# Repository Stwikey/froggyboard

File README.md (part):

# Keroppi

A cozy keyboard with every add-on you can think of! Keroppi is a wired keyboard, powered by a Raspberry Pi Pico through a modern USB-C port. It resembles a 75% keyboard layout style with 79 keys and also features a rotary encoder that can be used to toggle many short cuts such as turning the volume up or down. It also acts as another switch! There is also a TFT LCD screen that can display all sorts of images as you type! Finally, Keroppi has per key RGB lighting, and plays cool lighting animations on the keyboard!

# What does Keroppi do?

Keroppi is a wired keyboard that can be connected to your computer so you can start typing comfortably! it comes with cool components such as per-key RGB backlighting that plays animations as you type, a rotary encoder, and a TFT LCD screen that can display cool images or animations! Keroppi was designed to be an "all in one" keyboard, at least it's everything that I would want in a keyboard :D

# Why does Keroppi exist?

I've never owned a keyboard before despite being on my computer all day so I thought this was the perfect time to make one from scratch! Plus I'd be able to add as many features as I want and completely personalize it :D

# How do you use Keroppi?

## Assembly Instructions

#### 1. Handsoldering the PCB

Start by assembling the PCB! Handsolder all of the components onto the the PCB board according to the silkscreen diagram, that includes any LEDs, capacitors, resistors, pin headers, Raspberry Pi Pico, USB-C, TFT LCD, rotary encoder, and hotswap sockets.

The bottom should look something like this

The top should look something like this 

#### 1.5. Soldering the Data Lines

Twist two jumper wires together, trying to keep them the same length. Solder one of the jumper wires from TP2 on the Raspberry Pi Pico to D- and a jumper wire from TP3 on the Raspberry Pi Pico to D+ to connect the data lines.

Please note that although this method can work, it is still risky as data may not be able to establish a reliable connection. If this happens and you see data is not being transferred well, you can simply just use the usb port instead of the usb-c port.

#### 2. Assembling the Switch Plate

Assemble the switch plate by sliding in the stabilizers to their respective mounts

#### 3. Attach the Base

Install M2 female–male hex spacers in the base mounting holes and space out the switch plate from the PCB using 4mm spacers, next screw the layers in using a M2 screws inserted from the switch plate

#### 4. Attach the top plate

Slide in the top plate and it should hold screwless using friction! 

#### 5. Insert the switches

You can now insert the switches through the hotswap sockets

#### 6. Attach the keycaps

Attach the keycaps onto the switches

#### 7. Flashing Firmware

Simply start by putting the Raspberry Pi Pico into bootloader mode by plugging it into a USB port and pressing down the BOOTSEL button, once you see RPI-RPI2 open on your computer, drag the frogboard_default.uf2 file onto it (found in the firmware folder of this github repository) and you are ready to start typing!

# Schematic

## Switch Matrix

## RGB Daisy Chain

## Other Components

# PCB

## 3D Viewer Front

## 3D Viewer Back

# 3D Model

# BOM

|Item                                    |Qty Required|Qty*|Unit Price(CAD)|Total Price(CAD)**|URL                                                                                                                                                                                                                                                                                                                                                                                                                                                                                                                                                                                                                                                                                                                                                                                                                                                                                                                                                                              |
|----------------------------------------|------------|----|---------------|------------------|---------------------------------------------------------------------------------------------------------------------------------------------------------------------------------------------------------------------------------------------------------------------------------------------------------------------------------------------------------------------------------------------------------------------------------------------------------------------------------------------------------------------------------------------------------------------------------------------------------------------------------------------------------------------------------------------------------------------------------------------------------------------------------------------------------------------------------------------------------------------------------------------------------------------------------------------------------------------------------|
|Keyboard PCB                            |1           |5   |8.64           |43.18             |https://cart.jlcpcb.com/quote?stencilLayer=2&stencilWidth=100&stencilLength=100&stencilCounts=5&plateType=1&spm=Jlcpcb.Homepage.1010                                                                                                                                                                                                                                                                                                                                                                                                                                                                                                                                                                                                                                                                                                                                                                                                                                             |
|SK6812 MINI-E                           |80          |100 |0.07           |7.25              |https://www.aliexpress.com/item/1005005186515165.html?spm=a2g0o.detail.0.0.14e4nNtznNtzOB&mp=1&pdp_npi=6%40dis%21CAD%21CAD+7.25%21CAD+4.73%21%21CAD+4.73%21%21%21%40210328db17820150712871148e708f%2112000032026120161%21ct%21CA%217828448027%21%211%210%21                                                                                                                                                                                                                                                                                                                                                                                                                                                                                                                                                                                                                                                                                                                      |
|Kailh Hot-swappable Sockets             |80          |90  |0.23           |21.13             |https://www.aliexpress.com/item/1005002240956679.html?spm=a2g0o.detail.0.0.2181UnstUnstwW&mp=1&pdp_npi=6%40dis%21CAD%21CAD+15.74%21CAD+14.48%21%21CAD+14.48%21%21%21%402103122117820143535241604ec58f%2112000048872238968%21ct%21CA%217828448027%21%211%210%21                                                                                                                                                                                                                                                                                                                                                                                                                                                                                                                                                                                                                                                                                                                   |
|Gateron Clear Yellow MX Switches        |80          |90  |0.4            |36.4              |https://www.aliexpress.com/item/1005006376024657.html?spm=a2g0o.productlist.0.0.2aa56NJI6NJIrj&mp=1&pdp_npi=6%40dis%21CAD%21CAD+36.40%21CAD+21.93%21%21CAD+21.93%21%21%21%402103122117820135581002130ec58f%2112000036949493878%21ct%21CA%217828448027%21%211%210%21                                                                                                                                                                                                                                                                                                                                                                                                                                                                                                                                                                                                                                                                                                              |
|Green PBT Keycaps Cherry Profile        |80          |1   |41.48          |41.48             |https://www.aliexpress.com/item/1005011698106230.html?spm=a2g0o.productlist.main.26.2aa56NJI6NJIrj&algo_pvid=a63b7bbd-3eb6-4d5e-be3b-470bf1dd58c0&algo_exp_id=a63b7bbd-3eb6-4d5e-be3b-470bf1dd58c0-25&pdp_ext_f=%7B%22order%22%3A%224%22%2C%22eval%22%3A%221%22%2C%22fromPage%22%3A%22search%22%7D&pdp_npi=6%40dis%21CAD%2138.73%2124.79%21%21%2126.76%2117.13%21%402101d97817820135325363822e8929%2112000056278234003%21sea%21CA%217828448027%21ABX%211%210%21n_tag%3A-29910%3Bd%3A3dfa8a49%3Bm03_new_user%3A-29895&curPageLogUid=LUT1sxCeVqjB&utparam-url=scene%3Asearch%7Cquery_from%3A%7Cx_object_id%3A1005011698106230%7C_p_origin_prod%3A                                                                                                                                                                                                                                                                                                                                  |
|Raspberry Pi Pico                       |1           |1   |9.61           |9.61              |https://www.aliexpress.com/item/1005008488567735.html?spm=a2g0o.productlist.main.11.6d9c53d3w4FjBK&algo_pvid=b0a8d1be-a12d-493a-86f7-4a413408928d&algo_exp_id=b0a8d1be-a12d-493a-86f7-4a413408928d-10&pdp_ext_f=%7B%22order%22%3A%22238%22%2C%22spu_best_type%22%3A%22price%22%2C%22eval%22%3A%221%22%2C%22fromPage%22%3A%22search%22%7D&pdp_npi=6%40dis%21BDT%21306.37%21214.44%21%21%2117.53%2112.27%21%40210123bc17663989641772421e2e0d%2112000045364738896%21sea%21BD%21890572683%21ACX%211%210%21n_tag%3A-29919%3Bd%3A22373611%3Bm03_new_user%3A-29894&curPageLogUid=FYVvLIyyXM7I&utparam-url=scene%3Asearch%7Cquery_from%3A%7Cx_object_id%3A1005008488567735%7C_p_origin_prod%3A&aff_fcid=dce61beefcb647389e1909da4bce83fa-1782018134546-06343-_c2z7Inq5&tt=CPS_NORMAL&aff_fsk=_c2z7Inq5&aff_platform=portals-tool&sk=_c2z7Inq5&aff_trace_key=dce61beefcb647389e1909da4bce83fa-1782018134546-06343-_c2z7Inq5&terminal_id=a6aab7e9213e44ec8460500731546a6b&afSmartRedirect=y|
|Pin Header Kit for Raspberry Pi Pico    |1           |1   |4.34           |4.34              |https://www.aliexpress.com/item/1005011890511721.html?spm=a2g0o.productlist.main.3.1ad5tGTPtGTPhq&algo_pvid=d3ff1000-c459-4608-995b-4cd78ddb5e55&algo_exp_id=d3ff1000-c459-4608-995b-4cd78ddb5e55-2&pdp_ext_f=%7B%22order%22%3A%2215%22%2C%22eval%22%3A%221%22%2C%22fromPage%22%3A%22search%22%7D&pdp_npi=6%40dis%21CAD%214.34%211.76%21%21%213.00%211.22%21%40210319b717820182038143891e742a%2112000056910353722%21sea%21CA%217828448027%21ABX%211%210%21n_tag%3A-29910%3Bd%3A3dfa8a49%3Bm03_new_user%3A-29895%3BpisId%3A5000000207284321&curPageLogUid=W7DVBS57MRTf&utparam-url=scene%3Asearch%7Cquery_from%3A%7Cx_object_id%3A1005011890511721%7C_p_origin_prod%3A                                                                                                                                                                                                                                                                                                            |
|Plate-Mounted Stabilizers (4x2u 1x6.25u)|1           |1   |13.53          |13.53             |https://www.aliexpress.com/item/1005001840872635.html?spm=a2g0o.productlist.main.2.56c1bdGkbdGkkp&algo_pvid=00fce70c-ea1d-4432-9239-21779d81a662&algo_exp_id=00fce70c-ea1d-4432-9239-21779d81a662-1&pdp_ext_f=%7B%22order%22%3A%2249%22%2C%22eval%22%3A%221%22%2C%22fromPage%22%3A%22search%22%7D&pdp_npi=6%40dis%21CAD%2112.61%2111.86%21%21%218.71%218.19%21%402101f54117820190635584331e43ce%2112000017814370416%21sea%21CA%217828448027%21ABX%211%210%21n_tag%3A-29910%3Bd%3A3dfa8a49%3Bm03_new_user%3A-29895%3BpisId%3A5000000206226397&curPageLogUid=Rhk2c3Va2c9G&utparam-url=scene%3Asearch%7Cquery_from%3A%7Cx_object_id%3A1005001840872635%7C_p_origin_prod%3A                                                                                                                                                                                                                                                                                                          |
|Rotary Encoder Knob                     |1           |1   |3.73           |3.73              |https://www.aliexpress.com/item/1005008610645902.html?spm=a2g0o.productlist.main.8.4cff5da5nSD5Jc&aem_p4p_detail=202606202214172048192130410400002043741&algo_pvid=8607e45e-3412-46d6-a5e9-5ea0b7fe92e8&algo_exp_id=8607e45e-3412-46d6-a5e9-5ea0b7fe92e8-7&pdp_ext_f=%7B%22order%22%3A%22331%22%2C%22eval%22%3A%221%22%2C%22fromPage%22%3A%22search%22%7D&pdp_npi=6%40dis%21CAD%214.46%214.35%21%21%213.08%213.00%21%402103274e17820188572767577e2c45%2112000045944331228%21sea%21CA%217828448027%21ABX%211%210%21n_tag%3A-29910%3Bd%3A3dfa8a49%3Bm03_new_user%3A-29895%3BpisId%3A5000000206226397&curPageLogUid=fTDSHgs01fhl&utparam-url=scene%3Asearch%7Cquery_from%3A%7Cx_object_id%3A1005008610645902%7C_p_origin_prod%3A&search_p4p_id=202606202214172048192130410400002043741_2                                                                                                                                                                                            |
|EC11 Rotary Encoder Plum Axis           |1           |5   |16.37          |16.37             |https://www.aliexpress.com/item/1005011653314162.html?spm=a2g0o.productlist.main.14.7409ad7cFDtCjN&algo_pvid=aa1ff48c-15cf-44ad-98d6-0949c748634a&algo_exp_id=aa1ff48c-15cf-44ad-98d6-0949c748634a-13&pdp_ext_f=%7B%22order%22%3A%228%22%2C%22eval%22%3A%221%22%2C%22fromPage%22%3A%22search%22%7D&pdp_npi=6%40dis%21CAD%2116.25%217.63%21%21%2176.14%2135.74%21%402101e07217820186783357548e5ace%2112000056158778317%21sea%21CA%217828448027%21ABX%211%210%21n_tag%3A-29910%3Bd%3A3dfa8a49%3Bm03_new_user%3A-29895%3BpisId%3A5000000206226397&curPageLogUid=7R8KvrnWqpem&utparam-url=scene%3Asearch%7Cquery_from%3A%7Cx_object_id%3A1005011653314162%7C_p_origin_prod%3A                                                                                                                                                                                                                                                                                                        |
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
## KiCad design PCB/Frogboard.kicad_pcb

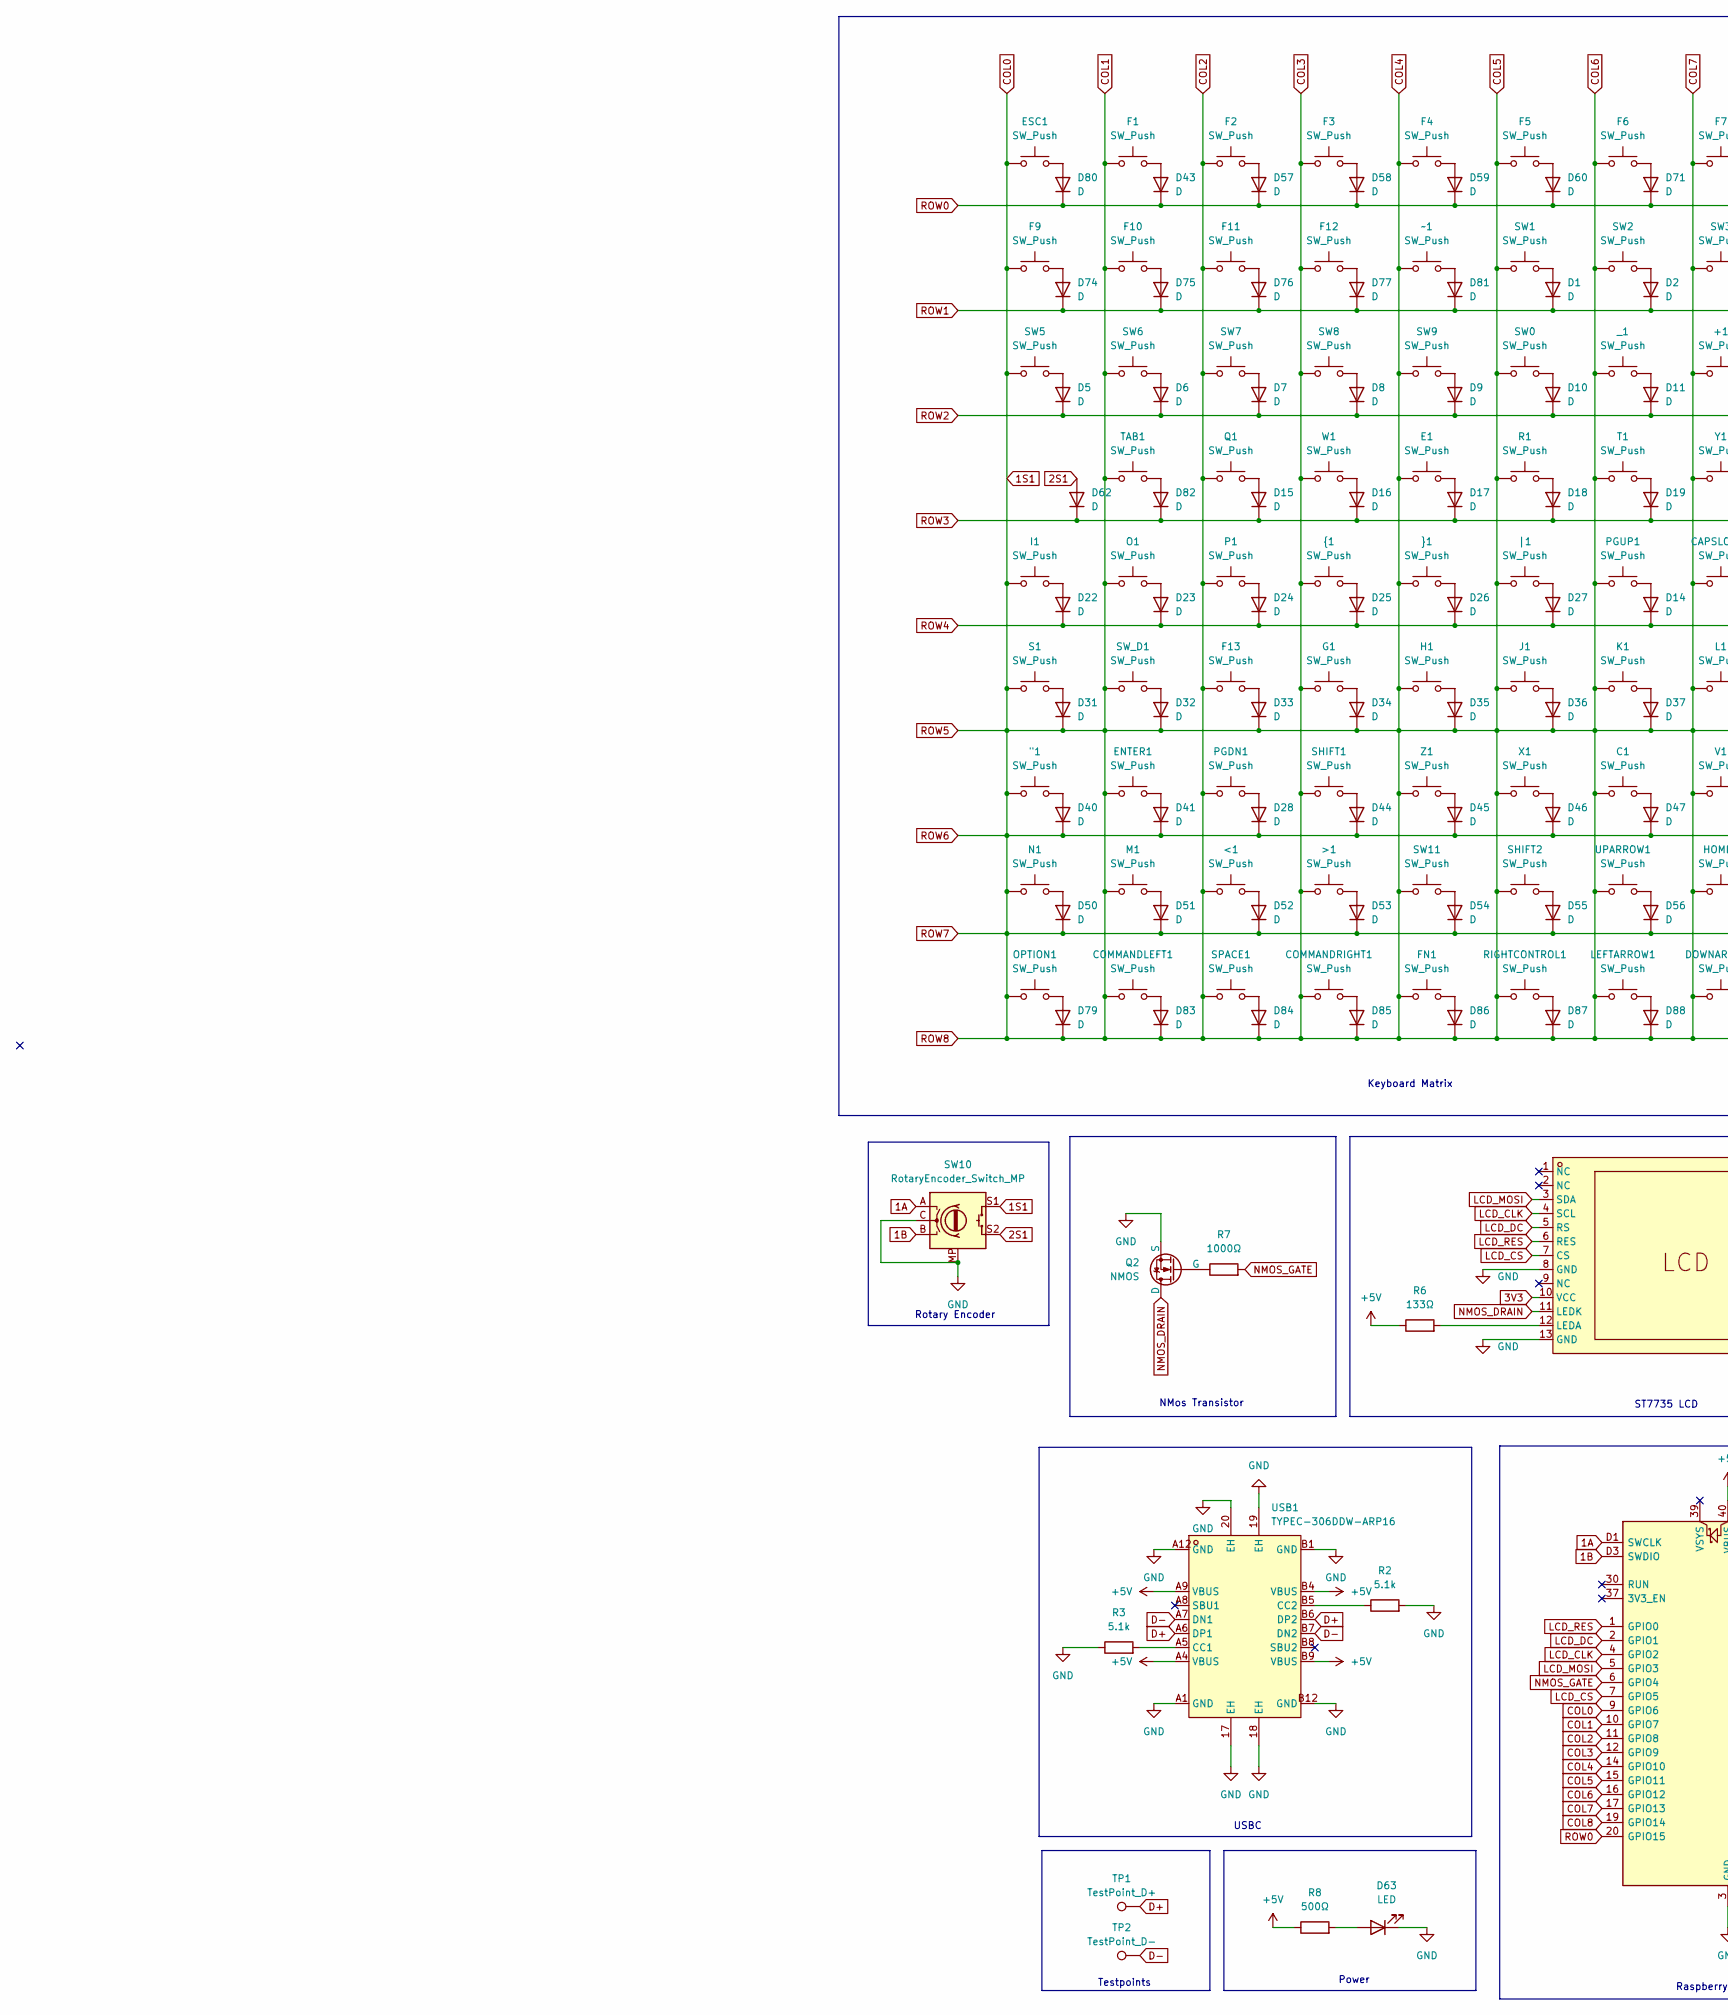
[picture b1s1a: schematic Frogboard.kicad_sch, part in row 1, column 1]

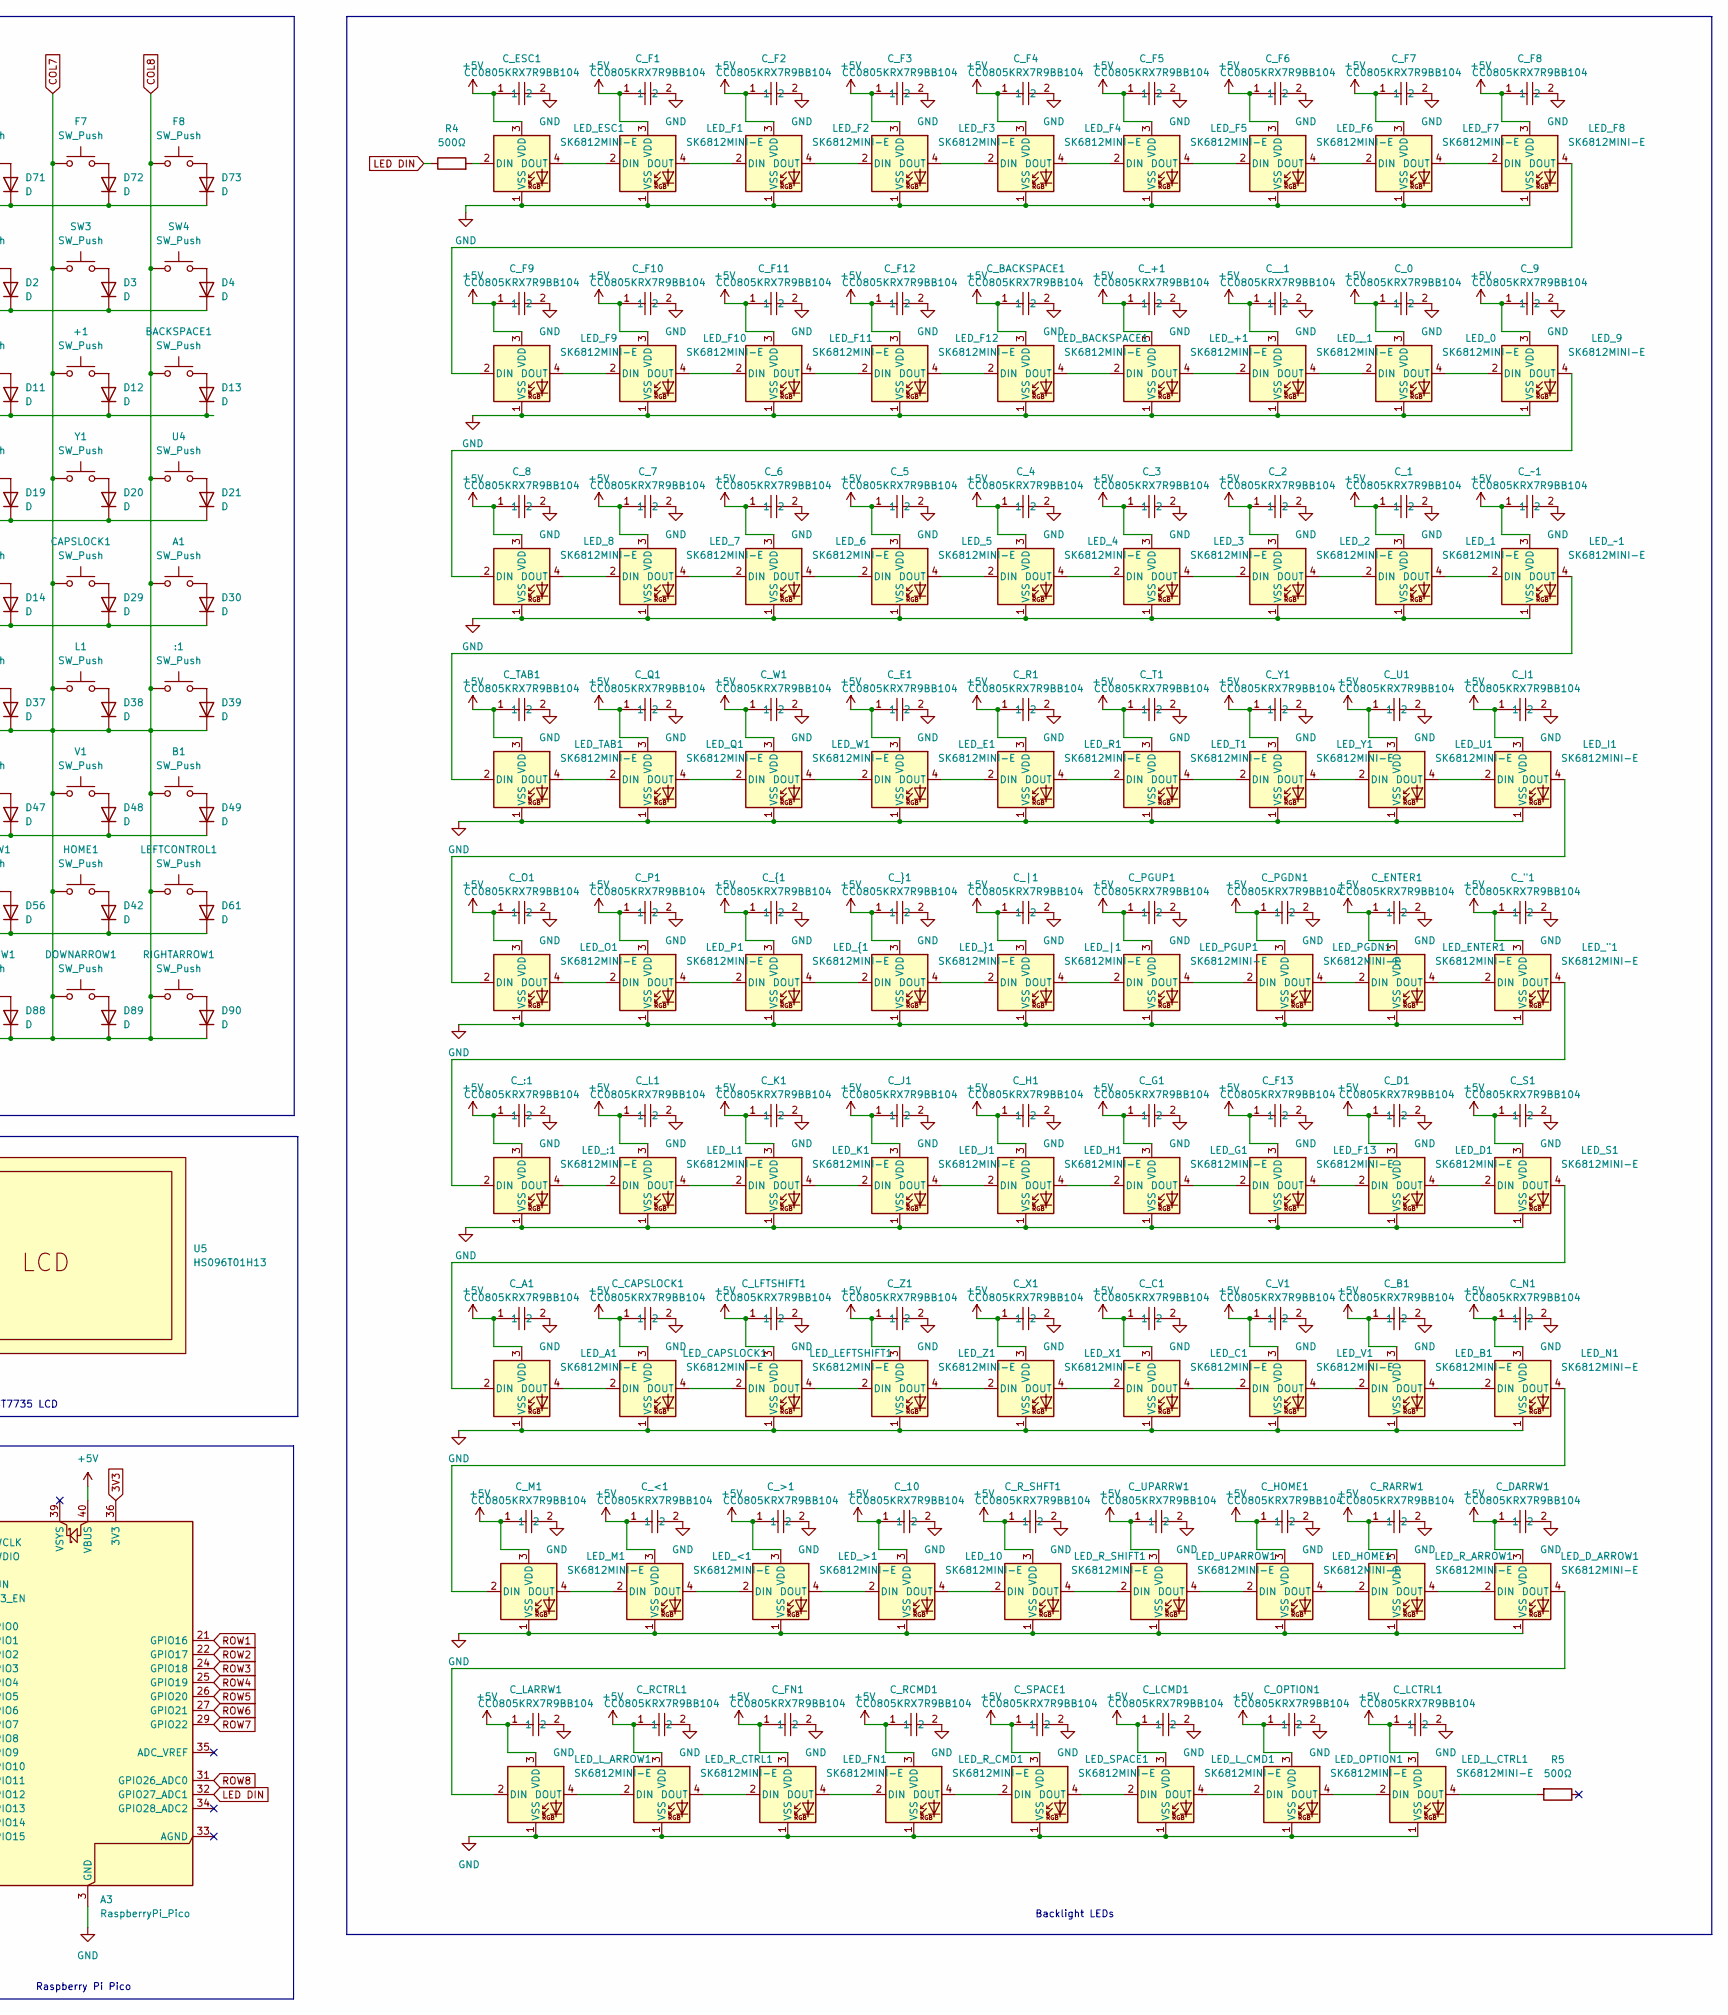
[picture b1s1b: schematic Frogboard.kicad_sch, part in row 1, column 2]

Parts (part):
"1: SW_Push; SW_MX_HS_CPG151101S11_1u
+1: SW_Push; SW_MX_HS_CPG151101S11_1u
:1: SW_Push; SW_MX_HS_CPG151101S11_1u
<1: SW_Push; SW_MX_HS_CPG151101S11_1u
>1: SW_Push; SW_MX_HS_CPG151101S11_1u
A1: SW_Push; SW_MX_HS_CPG151101S11_1u
A3: RaspberryPi_Pico; RaspberryPi_Pico_SMD_HandSolder
B1: SW_Push; SW_MX_HS_CPG151101S11_1u
BACKSPACE1: SW_Push; SW_MX_HS_CPG151101S11_1u
C1: SW_Push; SW_MX_HS_CPG151101S11_1u
CAPSLOCK1: SW_Push; SW_MX_HS_CPG151101S11_1.75u
COMMANDLEFT1: SW_Push; SW_MX_HS_CPG151101S11_1.25u
COMMANDRIGHT1: SW_Push; SW_MX_HS_CPG151101S11_1u
C_0, C_1, C_2, C_3, C_4, C_5, C_6, C_7, C_8, C_9, C_10: CC0805KRX7R9BB104; C_0805_2012Metric_Pad1.18x1.45mm_HandSolder; MPN CC0805KRX7R9BB104; LCSC Part C49678
C_"1: CC0805KRX7R9BB104; C_0805_2012Metric_Pad1.18x1.45mm_HandSolder; MPN CC0805KRX7R9BB104; LCSC Part C49678
C_+1: CC0805KRX7R9BB104; C_0805_2012Metric_Pad1.18x1.45mm_HandSolder; MPN CC0805KRX7R9BB104; LCSC Part C49678
C_:1: CC0805KRX7R9BB104; C_0805_2012Metric_Pad1.18x1.45mm_HandSolder; MPN CC0805KRX7R9BB104; LCSC Part C49678
C_<1: CC0805KRX7R9BB104; C_0805_2012Metric_Pad1.18x1.45mm_HandSolder; MPN CC0805KRX7R9BB104; LCSC Part C49678
C_>1: CC0805KRX7R9BB104; C_0805_2012Metric_Pad1.18x1.45mm_HandSolder; MPN CC0805KRX7R9BB104; LCSC Part C49678
C_A1: CC0805KRX7R9BB104; C_0805_2012Metric_Pad1.18x1.45mm_HandSolder; MPN CC0805KRX7R9BB104; LCSC Part C49678
C_B1: CC0805KRX7R9BB104; C_0805_2012Metric_Pad1.18x1.45mm_HandSolder; MPN CC0805KRX7R9BB104; LCSC Part C49678
C_BACKSPACE1: CC0805KRX7R9BB104; C_0805_2012Metric_Pad1.18x1.45mm_HandSolder; MPN CC0805KRX7R9BB104; LCSC Part C49678
C_C1: CC0805KRX7R9BB104; C_0805_2012Metric_Pad1.18x1.45mm_HandSolder; MPN CC0805KRX7R9BB104; LCSC Part C49678
C_CAPSLOCK1: CC0805KRX7R9BB104; C_0805_2012Metric_Pad1.18x1.45mm_HandSolder; MPN CC0805KRX7R9BB104; LCSC Part C49678
C_D1: CC0805KRX7R9BB104; C_0805_2012Metric_Pad1.18x1.45mm_HandSolder; MPN CC0805KRX7R9BB104; LCSC Part C49678
C_DARRW1: CC0805KRX7R9BB104; C_0805_2012Metric_Pad1.18x1.45mm_HandSolder; MPN CC0805KRX7R9BB104; LCSC Part C49678
C_E1: CC0805KRX7R9BB104; C_0805_2012Metric_Pad1.18x1.45mm_HandSolder; MPN CC0805KRX7R9BB104; LCSC Part C49678
C_ENTER1: CC0805KRX7R9BB104; C_0805_2012Metric_Pad1.18x1.45mm_HandSolder; MPN CC0805KRX7R9BB104; LCSC Part C49678
C_ESC1: CC0805KRX7R9BB104; C_0805_2012Metric_Pad1.18x1.45mm_HandSolder; MPN CC0805KRX7R9BB104; LCSC Part C49678
C_F1, C_F2, C_F3, C_F4, C_F5, C_F6, C_F7, C_F8, C_F9, C_F10, C_F11, C_F12, C_F13: CC0805KRX7R9BB104; C_0805_2012Metric_Pad1.18x1.45mm_HandSolder; MPN CC0805KRX7R9BB104; LCSC Part C49678
C_FN1: CC0805KRX7R9BB104; C_0805_2012Metric_Pad1.18x1.45mm_HandSolder; MPN CC0805KRX7R9BB104; LCSC Part C49678
C_G1: CC0805KRX7R9BB104; C_0805_2012Metric_Pad1.18x1.45mm_HandSolder; MPN CC0805KRX7R9BB104; LCSC Part C49678
C_H1: CC0805KRX7R9BB104; C_0805_2012Metric_Pad1.18x1.45mm_HandSolder; MPN CC0805KRX7R9BB104; LCSC Part C49678
C_HOME1: CC0805KRX7R9BB104; C_0805_2012Metric_Pad1.18x1.45mm_HandSolder; MPN CC0805KRX7R9BB104; LCSC Part C49678
C_I1: CC0805KRX7R9BB104; C_0805_2012Metric_Pad1.18x1.45mm_HandSolder; MPN CC0805KRX7R9BB104; LCSC Part C49678
C_J1: CC0805KRX7R9BB104; C_0805_2012Metric_Pad1.18x1.45mm_HandSolder; MPN CC0805KRX7R9BB104; LCSC Part C49678
C_K1: CC0805KRX7R9BB104; C_0805_2012Metric_Pad1.18x1.45mm_HandSolder; MPN CC0805KRX7R9BB104; LCSC Part C49678
C_L1: CC0805KRX7R9BB104; C_0805_2012Metric_Pad1.18x1.45mm_HandSolder; MPN CC0805KRX7R9BB104; LCSC Part C49678
C_LARRW1: CC0805KRX7R9BB104; C_0805_2012Metric_Pad1.18x1.45mm_HandSolder; MPN CC0805KRX7R9BB104; LCSC Part C49678
C_LCMD1: CC0805KRX7R9BB104; C_0805_2012Metric_Pad1.18x1.45mm_HandSolder; MPN CC0805KRX7R9BB104; LCSC Part C49678
C_LCTRL1: CC0805KRX7R9BB104; C_0805_2012Metric_Pad1.18x1.45mm_HandSolder; MPN CC0805KRX7R9BB104; LCSC Part C49678
C_LFTSHIFT1: CC0805KRX7R9BB104; C_0805_2012Metric_Pad1.18x1.45mm_HandSolder; MPN CC0805KRX7R9BB104; LCSC Part C49678
C_M1: CC0805KRX7R9BB104; C_0805_2012Metric_Pad1.18x1.45mm_HandSolder; MPN CC0805KRX7R9BB104; LCSC Part C49678
C_N1: CC0805KRX7R9BB104; C_0805_2012Metric_Pad1.18x1.45mm_HandSolder; MPN CC0805KRX7R9BB104; LCSC Part C49678
C_O1: CC0805KRX7R9BB104; C_0805_2012Metric_Pad1.18x1.45mm_HandSolder; MPN CC0805KRX7R9BB104; LCSC Part C49678
C_OPTION1: CC0805KRX7R9BB104; C_0805_2012Metric_Pad1.18x1.45mm_HandSolder; MPN CC0805KRX7R9BB104; LCSC Part C49678
C_P1: CC0805KRX7R9BB104; C_0805_2012Metric_Pad1.18x1.45mm_HandSolder; MPN CC0805KRX7R9BB104; LCSC Part C49678
C_PGDN1: CC0805KRX7R9BB104; C_0805_2012Metric_Pad1.18x1.45mm_HandSolder; MPN CC0805KRX7R9BB104; LCSC Part C49678
C_PGUP1: CC0805KRX7R9BB104; C_0805_2012Metric_Pad1.18x1.45mm_HandSolder; MPN CC0805KRX7R9BB104; LCSC Part C49678
C_Q1: CC0805KRX7R9BB104; C_0805_2012Metric_Pad1.18x1.45mm_HandSolder; MPN CC0805KRX7R9BB104; LCSC Part C49678
C_R1: CC0805KRX7R9BB104; C_0805_2012Metric_Pad1.18x1.45mm_HandSolder; MPN CC0805KRX7R9BB104; LCSC Part C49678
C_RARRW1: CC0805KRX7R9BB104; C_0805_2012Metric_Pad1.18x1.45mm_HandSolder; MPN CC0805KRX7R9BB104; LCSC Part C49678
C_RCMD1: CC0805KRX7R9BB104; C_0805_2012Metric_Pad1.18x1.45mm_HandSolder; MPN CC0805KRX7R9BB104; LCSC Part C49678
C_RCTRL1: CC0805KRX7R9BB104; C_0805_2012Metric_Pad1.18x1.45mm_HandSolder; MPN CC0805KRX7R9BB104; LCSC Part C49678
C_R_SHFT1: CC0805KRX7R9BB104; C_0805_2012Metric_Pad1.18x1.45mm_HandSolder; MPN CC0805KRX7R9BB104; LCSC Part C49678
C_S1: CC0805KRX7R9BB104; C_0805_2012Metric_Pad1.18x1.45mm_HandSolder; MPN CC0805KRX7R9BB104; LCSC Part C49678
C_SPACE1: CC0805KRX7R9BB104; C_0805_2012Metric_Pad1.18x1.45mm_HandSolder; MPN CC0805KRX7R9BB104; LCSC Part C49678
C_T1: CC0805KRX7R9BB104; C_0805_2012Metric_Pad1.18x1.45mm_HandSolder; MPN CC0805KRX7R9BB104; LCSC Part C49678
C_TAB1: CC0805KRX7R9BB104; C_0805_2012Metric_Pad1.18x1.45mm_HandSolder; MPN CC0805KRX7R9BB104; LCSC Part C49678
C_U1: CC0805KRX7R9BB104; C_0805_2012Metric_Pad1.18x1.45mm_HandSolder; MPN CC0805KRX7R9BB104; LCSC Part C49678
C_UPARRW1: CC0805KRX7R9BB104; C_0805_2012Metric_Pad1.18x1.45mm_HandSolder; MPN CC0805KRX7R9BB104; LCSC Part C49678
C_V1: CC0805KRX7R9BB104; C_0805_2012Metric_Pad1.18x1.45mm_HandSolder; MPN CC0805KRX7R9BB104; LCSC Part C49678
C_W1: CC0805KRX7R9BB104; C_0805_2012Metric_Pad1.18x1.45mm_HandSolder; MPN CC0805KRX7R9BB104; LCSC Part C49678
C_X1: CC0805KRX7R9BB104; C_0805_2012Metric_Pad1.18x1.45mm_HandSolder; MPN CC0805KRX7R9BB104; LCSC Part C49678
C_Y1: CC0805KRX7R9BB104; C_0805_2012Metric_Pad1.18x1.45mm_HandSolder; MPN CC0805KRX7R9BB104; LCSC Part C49678
C_Z1: CC0805KRX7R9BB104; C_0805_2012Metric_Pad1.18x1.45mm_HandSolder; MPN CC0805KRX7R9BB104; LCSC Part C49678
C__1: CC0805KRX7R9BB104; C_0805_2012Metric_Pad1.18x1.45mm_HandSolder; MPN CC0805KRX7R9BB104; LCSC Part C49678
C_{1: CC0805KRX7R9BB104; C_0805_2012Metric_Pad1.18x1.45mm_HandSolder; MPN CC0805KRX7R9BB104; LCSC Part C49678
C_|1: CC0805KRX7R9BB104; C_0805_2012Metric_Pad1.18x1.45mm_HandSolder; MPN CC0805KRX7R9BB104; LCSC Part C49678
C_}1: CC0805KRX7R9BB104; C_0805_2012Metric_Pad1.18x1.45mm_HandSolder; MPN CC0805KRX7R9BB104; LCSC Part C49678
C_~1: CC0805KRX7R9BB104; C_0805_2012Metric_Pad1.18x1.45mm_HandSolder; MPN CC0805KRX7R9BB104; LCSC Part C49678
D1, D2, D3, D4, D5, D6, D7, D8, D9, D10, D11, D12, D13, D14, D15, D16, D17, D18, D19, D20, D21, D22, D23, D24, D25, D26, D27, D28, D29, D30, D31, D32, D33, D34, D35, D36, D37, D38, D39, D40, D41, D42, D43, D44, D45, D46, D47, D48, D49, D50, D51, D52, D53, D54, D55, D56, D57, D58, D59, D60, D61, D62, D71, D72, D73, D74, D75, D76, D77, D79, D80, D81, D82, D83, D84, D85, D86, D87, D88, D89, D90: D; D_SOD-123
D63: LED; LED_D5.0mm
DOWNARROW1: SW_Push; SW_MX_HS_CPG151101S11_1u
E1: SW_Push; SW_MX_HS_CPG151101S11_1u
ENTER1: SW_Push; SW_MX_HS_CPG151101S11_1u
ESC1: SW_Push; SW_MX_HS_CPG151101S11_1u
F1, F2, F3, F4, F5, F6, F7, F8, F9, F10, F11, F12, F13: SW_Push; SW_MX_HS_CPG151101S11_1u
FN1: SW_Push; SW_MX_HS_CPG151101S11_1u
G1: SW_Push; SW_MX_HS_CPG151101S11_1u
H1: SW_Push; SW_MX_HS_CPG151101S11_1u
HOME1: SW_Push; SW_MX_HS_CPG151101S11_1u
I1: SW_Push; SW_MX_HS_CPG151101S11_1u
J1: SW_Push; SW_MX_HS_CPG151101S11_1u
K1: SW_Push; SW_MX_HS_CPG151101S11_1u
L1: SW_Push; SW_MX_HS_CPG151101S11_1u
LED_0, LED_1, LED_2, LED_3, LED_4, LED_5, LED_6, LED_7, LED_8, LED_9, LED_10: SK6812MINI-E; LED_SK6812MINI-E_3.2x2.8mm_P1.5mm_ReverseMount
LED_"1: SK6812MINI-E; LED_SK6812MINI-E_3.2x2.8mm_P1.5mm_ReverseMount
LED_+1: SK6812MINI-E; LED_SK6812MINI-E_3.2x2.8mm_P1.5mm_ReverseMount
LED_:1: SK6812MINI-E; LED_SK6812MINI-E_3.2x2.8mm_P1.5mm_ReverseMount
LED_<1: SK6812MINI-E; LED_SK6812MINI-E_3.2x2.8mm_P1.5mm_ReverseMount
LED_>1: SK6812MINI-E; LED_SK6812MINI-E_3.2x2.8mm_P1.5mm_ReverseMount
LED_A1: SK6812MINI-E; LED_SK6812MINI-E_3.2x2.8mm_P1.5mm_ReverseMount
LED_B1: SK6812MINI-E; LED_SK6812MINI-E_3.2x2.8mm_P1.5mm_ReverseMount
LED_BACKSPACE1: SK6812MINI-E; LED_SK6812MINI-E_3.2x2.8mm_P1.5mm_ReverseMount
LED_C1: SK6812MINI-E; LED_SK6812MINI-E_3.2x2.8mm_P1.5mm_ReverseMount
LED_CAPSLOCK1: SK6812MINI-E; LED_SK6812MINI-E_3.2x2.8mm_P1.5mm_ReverseMount
LED_D1: SK6812MINI-E; LED_SK6812MINI-E_3.2x2.8mm_P1.5mm_ReverseMount
LED_D_ARROW1: SK6812MINI-E; LED_SK6812MINI-E_3.2x2.8mm_P1.5mm_ReverseMount
LED_E1: SK6812MINI-E; LED_SK6812MINI-E_3.2x2.8mm_P1.5mm_ReverseMount
LED_ENTER1: SK6812MINI-E; LED_SK6812MINI-E_3.2x2.8mm_P1.5mm_ReverseMount
LED_ESC1: SK6812MINI-E; LED_SK6812MINI-E_3.2x2.8mm_P1.5mm_ReverseMount
LED_F1, LED_F2, LED_F3, LED_F4, LED_F5, LED_F6, LED_F7, LED_F8, LED_F9, LED_F10, LED_F11, LED_F12, LED_F13: SK6812MINI-E; LED_SK6812MINI-E_3.2x2.8mm_P1.5mm_ReverseMount
LED_FN1: SK6812MINI-E; LED_SK6812MINI-E_3.2x2.8mm_P1.5mm_ReverseMount
LED_G1: SK6812MINI-E; LED_SK6812MINI-E_3.2x2.8mm_P1.5mm_ReverseMount
LED_H1: SK6812MINI-E; LED_SK6812MINI-E_3.2x2.8mm_P1.5mm_ReverseMount
LED_HOME1: SK6812MINI-E; LED_SK6812MINI-E_3.2x2.8mm_P1.5mm_ReverseMount
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
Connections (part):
1A: A3.D1 (SWCLK), SW10.A
1B: A3.D3 (SWDIO), SW10.B
1S1: "1.1, +1.1, :1.1, <1.1, >1.1, A1.1, A3.9 (GPIO6), A3.10 (GPIO7), A3.11 (GPIO8), A3.12 (GPIO9), A3.14 (GPIO10), A3.15 (GPIO11), A3.16 (GPIO12), A3.17 (GPIO13), A3.19 (GPIO14), A3.26 (GPIO20), A3.27 (GPIO21), A3.29 (GPIO22), A3.31 (GPIO26_ADC0), B1.1, BACKSPACE1.1, C1.1, CAPSLOCK1.1, COMMANDLEFT1.1, COMMANDRIGHT1.1, D28.1 (K), D31.1 (K), D32.1 (K), D33.1 (K), D34.1 (K), D35.1 (K), D36.1 (K), D37.1 (K), D38.1 (K), D39.1 (K), D40.1 (K), D41.1 (K), D42.1 (K), D44.1 (K), D45.1 (K), D46.1 (K), D47.1 (K), D48.1 (K), D49.1 (K), D50.1 (K), D51.1 (K), D52.1 (K), D53.1 (K), D54.1 (K), D55.1 (K), D56.1 (K), D61.1 (K), D79.1 (K), D83.1 (K), D84.1 (K), D85.1 (K), D86.1 (K), D87.1 (K), D88.1 (K), D89.1 (K), D90.1 (K), DOWNARROW1.1, E1.1, ENTER1.1, ESC1.1, F1.1, F2.1, F3.1, F4.1, F5.1, F6.1, F7.1, F8.1, F9.1, F10.1, F11.1, F12.1, F13.1, FN1.1, G1.1, H1.1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
2S1: D62.2 (A), SW10.S2
3V3: A3.36 (3V3), U5.10 (VCC)
+5V: A3.40 (VBUS), C_0.1, C_1.1, C_2.1, C_3.1, C_4.1, C_5.1, C_6.1, C_7.1, C_8.1, C_9.1, C_10.1, C_"1.1, C_+1.1, C_:1.1, C_<1.1, C_>1.1, C_A1.1, C_B1.1, C_BACKSPACE1.1, C_C1.1, C_CAPSLOCK1.1, C_D1.1, C_DARRW1.1, C_E1.1, C_ENTER1.1, C_ESC1.1, C_F1.1, C_F2.1, C_F3.1, C_F4.1, C_F5.1, C_F6.1, C_F7.1, C_F8.1, C_F9.1, C_F10.1, C_F11.1, C_F12.1, C_F13.1, C_FN1.1, C_G1.1, C_H1.1, C_HOME1.1, C_I1.1, C_J1.1, C_K1.1, C_L1.1, C_LARRW1.1, C_LCMD1.1, C_LCTRL1.1, C_LFTSHIFT1.1, C_M1.1, C_N1.1, C_O1.1, C_OPTION1.1, C_P1.1, C_PGDN1.1, C_PGUP1.1, C_Q1.1, C_R1.1, C_RARRW1.1, C_RCMD1.1, C_RCTRL1.1, C_R_SHFT1.1, C_S1.1, C_SPACE1.1, C_T1.1, C_TAB1.1, C_U1.1, C_UPARRW1.1, C_V1.1, C_W1.1, C_X1.1, C_Y1.1, C_Z1.1, C__1.1, C_{1.1, C_|1.1, C_}1.1, C_~1.1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
D+: TP1.1 (1_1), USB1.A6 (DP1), USB1.B6 (DP2)
D-: TP2.1 (1_1), USB1.A7 (DN1), USB1.B7 (DN2)
GND: A3.3 (GND), A3.8 (GND), A3.13 (GND), A3.18 (GND), A3.23 (GND), A3.28 (GND), A3.38 (GND), A3.D2 (GND), C_0.2, C_1.2, C_2.2, C_3.2, C_4.2, C_5.2, C_6.2, C_7.2, C_8.2, C_9.2, C_10.2, C_"1.2, C_+1.2, C_:1.2, C_<1.2, C_>1.2, C_A1.2, C_B1.2, C_BACKSPACE1.2, C_C1.2, C_CAPSLOCK1.2, C_D1.2, C_DARRW1.2, C_E1.2, C_ENTER1.2, C_ESC1.2, C_F1.2, C_F2.2, C_F3.2, C_F4.2, C_F5.2, C_F6.2, C_F7.2, C_F8.2, C_F9.2, C_F10.2, C_F11.2, C_F12.2, C_F13.2, C_FN1.2, C_G1.2, C_H1.2, C_HOME1.2, C_I1.2, C_J1.2, C_K1.2, C_L1.2, C_LARRW1.2, C_LCMD1.2, C_LCTRL1.2, C_LFTSHIFT1.2, C_M1.2, C_N1.2, C_O1.2, C_OPTION1.2, C_P1.2, C_PGDN1.2, C_PGUP1.2, C_Q1.2, C_R1.2, C_RARRW1.2, C_RCMD1.2, C_RCTRL1.2, C_R_SHFT1.2, C_S1.2, C_SPACE1.2, C_T1.2, C_TAB1.2, C_U1.2, C_UPARRW1.2, C_V1.2, C_W1.2, C_X1.2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
LCD_CLK: A3.4 (GPIO2), U5.4 (SCL)
LCD_CS: A3.7 (GPIO5), U5.7 (CS)
LCD_DC: A3.2 (GPIO1), U5.5 (RS)
LCD_MOSI: A3.5 (GPIO3), U5.3 (SDA)
LCD_RES: A3.1 (GPIO0), U5.6 (RES)
LED DIN: A3.32 (GPIO27_ADC1), R4.1
NMOS_DRAIN: Q2.1 (D), U5.11 (LEDK)
NMOS_GATE: A3.6 (GPIO4), R7.2
unnamed: D1.2 (A), SW1.2
unnamed: D2.2 (A), SW2.2
unnamed: D3.2 (A), SW3.2
unnamed: D4.2 (A), SW4.2
unnamed: D5.2 (A), SW5.2
unnamed: D6.2 (A), SW6.2
unnamed: D7.2 (A), SW7.2
unnamed: D8.2 (A), SW8.2
unnamed: D9.2 (A), SW9.2
unnamed: D10.2 (A), SW0.2
unnamed: D11.2 (A), _1.2
unnamed: +1.2, D12.2 (A)
unnamed: BACKSPACE1.2, D13.2 (A)
unnamed: D14.2 (A), PGUP1.2
unnamed: D15.2 (A), Q1.2
unnamed: D16.2 (A), W1.2
unnamed: D17.2 (A), E1.2
unnamed: D18.2 (A), R1.2
unnamed: D19.2 (A), T1.2
unnamed: D20.2 (A), Y1.2
unnamed: D21.2 (A), U4.2
unnamed: D22.2 (A), I1.2
unnamed: D23.2 (A), O1.2
unnamed: D24.2 (A), P1.2
unnamed: D25.2 (A), {1.2
unnamed: D26.2 (A), }1.2
unnamed: D27.2 (A), |1.2
unnamed: D28.2 (A), PGDN1.2
unnamed: CAPSLOCK1.2, D29.2 (A)
unnamed: A1.2, D30.2 (A)
unnamed: D31.2 (A), S1.2
unnamed: D32.2 (A), SW_D1.2
unnamed: D33.2 (A), F13.2
unnamed: D34.2 (A), G1.2
unnamed: D35.2 (A), H1.2
unnamed: D36.2 (A), J1.2
unnamed: D37.2 (A), K1.2
unnamed: D38.2 (A), L1.2
unnamed: :1.2, D39.2 (A)
unnamed: "1.2, D40.2 (A)
unnamed: D41.2 (A), ENTER1.2
unnamed: D42.2 (A), HOME1.2
unnamed: D43.2 (A), F1.2
unnamed: D44.2 (A), SHIFT1.2
unnamed: D45.2 (A), Z1.2
unnamed: D46.2 (A), X1.2
unnamed: C1.2, D47.2 (A)
unnamed: D48.2 (A), V1.2
unnamed: B1.2, D49.2 (A)
unnamed: D50.2 (A), N1.2
unnamed: D51.2 (A), M1.2
unnamed: <1.2, D52.2 (A)
unnamed: >1.2, D53.2 (A)
unnamed: D54.2 (A), SW11.2
unnamed: D55.2 (A), SHIFT2.2
unnamed: D56.2 (A), UPARROW1.2
unnamed: D57.2 (A), F2.2
unnamed: D58.2 (A), F3.2
unnamed: D59.2 (A), F4.2
unnamed: D60.2 (A), F5.2
unnamed: D61.2 (A), LEFTCONTROL1.2
unnamed: D63.2 (A), R8.2
unnamed: D71.2 (A), F6.2
unnamed: D72.2 (A), F7.2
unnamed: D73.2 (A), F8.2
unnamed: D74.2 (A), F9.2
unnamed: D75.2 (A), F10.2
unnamed: D76.2 (A), F11.2
unnamed: D77.2 (A), F12.2
unnamed: D79.2 (A), OPTION1.2
unnamed: D80.2 (A), ESC1.2
unnamed: D81.2 (A), ~1.2
unnamed: D82.2 (A), TAB1.2
unnamed: COMMANDLEFT1.2, D83.2 (A)
unnamed: D84.2 (A), SPACE1.2
unnamed: COMMANDRIGHT1.2, D85.2 (A)
unnamed: D86.2 (A), FN1.2
unnamed: D87.2 (A), RIGHTCONTROL1.2
unnamed: D88.2 (A), LEFTARROW1.2
unnamed: D89.2 (A), DOWNARROW1.2
unnamed: D90.2 (A), RIGHTARROW1.2
unnamed: LED_0.2 (DIN), LED__1.4 (DOUT)
unnamed: LED_0.4 (DOUT), LED_9.2 (DIN)
unnamed: LED_1.2 (DIN), LED_2.4 (DOUT)
unnamed: LED_1.4 (DOUT), LED_~1.2 (DIN)
unnamed: LED_2.2 (DIN), LED_3.4 (DOUT)
unnamed: LED_3.2 (DIN), LED_4.4 (DOUT)
unnamed: LED_4.2 (DIN), LED_5.4 (DOUT)
unnamed: LED_5.2 (DIN), LED_6.4 (DOUT)
unnamed: LED_6.2 (DIN), LED_7.4 (DOUT)
unnamed: LED_7.2 (DIN), LED_8.4 (DOUT)
unnamed: LED_8.2 (DIN), LED_9.4 (DOUT)
unnamed: LED_10.2 (DIN), LED_>1.4 (DOUT)
unnamed: LED_10.4 (DOUT), LED_R_SHIFT1.2 (DIN)
unnamed: LED_"1.2 (DIN), LED_ENTER1.4 (DOUT)
unnamed: LED_"1.4 (DOUT), LED_:1.2 (DIN)
unnamed: LED_+1.2 (DIN), LED_BACKSPACE1.4 (DOUT)
unnamed: LED_+1.4 (DOUT), LED__1.2 (DIN)
unnamed: LED_:1.4 (DOUT), LED_L1.2 (DIN)
unnamed: LED_<1.2 (DIN), LED_M1.4 (DOUT)
unnamed: LED_<1.4 (DOUT), LED_>1.2 (DIN)
unnamed: LED_A1.2 (DIN), LED_S1.4 (DOUT)
unnamed: LED_A1.4 (DOUT), LED_CAPSLOCK1.2 (DIN)
unnamed: LED_B1.2 (DIN), LED_V1.4 (DOUT)
unnamed: LED_B1.4 (DOUT), LED_N1.2 (DIN)
unnamed: LED_BACKSPACE1.2 (DIN), LED_F12.4 (DOUT)
unnamed: LED_C1.2 (DIN), LED_X1.4 (DOUT)
unnamed: LED_C1.4 (DOUT), LED_V1.2 (DIN)
unnamed: LED_CAPSLOCK1.4 (DOUT), LED_LEFTSHIFT1.2 (DIN)
unnamed: LED_D1.2 (DIN), LED_F13.4 (DOUT)
unnamed: LED_D1.4 (DOUT), LED_S1.2 (DIN)
unnamed: LED_D_ARROW1.2 (DIN), LED_R_ARROW1.4 (DOUT)
unnamed: LED_D_ARROW1.4 (DOUT), LED_L_ARROW1.2 (DIN)
unnamed: LED_E1.2 (DIN), LED_W1.4 (DOUT)
unnamed: LED_E1.4 (DOUT), LED_R1.2 (DIN)
unnamed: LED_ENTER1.2 (DIN), LED_PGDN1.4 (DOUT)
unnamed: LED_ESC1.2 (DIN), R4.2
unnamed: LED_ESC1.4 (DOUT), LED_F1.2 (DIN)
unnamed: LED_F1.4 (DOUT), LED_F2.2 (DIN)
unnamed: LED_F2.4 (DOUT), LED_F3.2 (DIN)
unnamed: LED_F3.4 (DOUT), LED_F4.2 (DIN)
unnamed: LED_F4.4 (DOUT), LED_F5.2 (DIN)
unnamed: LED_F5.4 (DOUT), LED_F6.2 (DIN)
unnamed: LED_F6.4 (DOUT), LED_F7.2 (DIN)
unnamed: LED_F7.4 (DOUT), LED_F8.2 (DIN)
unnamed: LED_F8.4 (DOUT), LED_F9.2 (DIN)
unnamed: LED_F9.4 (DOUT), LED_F10.2 (DIN)
unnamed: LED_F10.4 (DOUT), LED_F11.2 (DIN)
unnamed: LED_F11.4 (DOUT), LED_F12.2 (DIN)
unnamed: LED_F13.2 (DIN), LED_G1.4 (DOUT)
unnamed: LED_FN1.2 (DIN), LED_R_CTRL1.4 (DOUT)
unnamed: LED_FN1.4 (DOUT), LED_R_CMD1.2 (DIN)
unnamed: LED_G1.2 (DIN), LED_H1.4 (DOUT)
unnamed: LED_H1.2 (DIN), LED_J1.4 (DOUT)
unnamed: LED_HOME1.2 (DIN), LED_UPARROW1.4 (DOUT)
unnamed: LED_HOME1.4 (DOUT), LED_R_ARROW1.2 (DIN)
unnamed: LED_I1.2 (DIN), LED_U1.4 (DOUT)
unnamed: LED_I1.4 (DOUT), LED_O1.2 (DIN)
unnamed: LED_J1.2 (DIN), LED_K1.4 (DOUT)
unnamed: LED_K1.2 (DIN), LED_L1.4 (DOUT)
unnamed: LED_LEFTSHIFT1.4 (DOUT), LED_Z1.2 (DIN)
unnamed: LED_L_ARROW1.4 (DOUT), LED_R_CTRL1.2 (DIN)
unnamed: LED_L_CMD1.2 (DIN), LED_SPACE1.4 (DOUT)
unnamed: LED_L_CMD1.4 (DOUT), LED_OPTION1.2 (DIN)
unnamed: LED_L_CTRL1.2 (DIN), LED_OPTION1.4 (DOUT)
unnamed: LED_L_CTRL1.4 (DOUT), R5.2
unnamed: LED_M1.2 (DIN), LED_N1.4 (DOUT)
unnamed: LED_O1.4 (DOUT), LED_P1.2 (DIN)
unnamed: LED_P1.4 (DOUT), LED_{1.2 (DIN)
unnamed: LED_PGDN1.2 (DIN), LED_PGUP1.4 (DOUT)
unnamed: LED_PGUP1.2 (DIN), LED_|1.4 (DOUT)
unnamed: LED_Q1.2 (DIN), LED_TAB1.4 (DOUT)
unnamed: LED_Q1.4 (DOUT), LED_W1.2 (DIN)
unnamed: LED_R1.4 (DOUT), LED_T1.2 (DIN)
unnamed: LED_R_CMD1.4 (DOUT), LED_SPACE1.2 (DIN)
unnamed: LED_R_SHIFT1.4 (DOUT), LED_UPARROW1.2 (DIN)
unnamed: LED_T1.4 (DOUT), LED_Y1.2 (DIN)
unnamed: LED_TAB1.2 (DIN), LED_~1.4 (DOUT)
unnamed: LED_U1.2 (DIN), LED_Y1.4 (DOUT)
unnamed: LED_X1.2 (DIN), LED_Z1.4 (DOUT)
unnamed: LED_{1.4 (DOUT), LED_}1.2 (DIN)
unnamed: LED_|1.2 (DIN), LED_}1.4 (DOUT)
unnamed: Q2.2 (G), R7.1
unnamed: R6.2, U5.12 (LEDA)
unnamed: R3.2, USB1.A5 (CC1)
unnamed: R2.1, USB1.B5 (CC2)
ROW0: A3.20 (GPIO15), D43.1 (K), D57.1 (K), D58.1 (K), D59.1 (K), D60.1 (K), D71.1 (K), D72.1 (K), D73.1 (K), D80.1 (K)
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
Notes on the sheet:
Keyboard Matrix
Testpoints
NMos Transistor
Raspberry Pi Pico
USBC
Power
ST7735 LCD
Backlight LEDs
Rotary Encoder

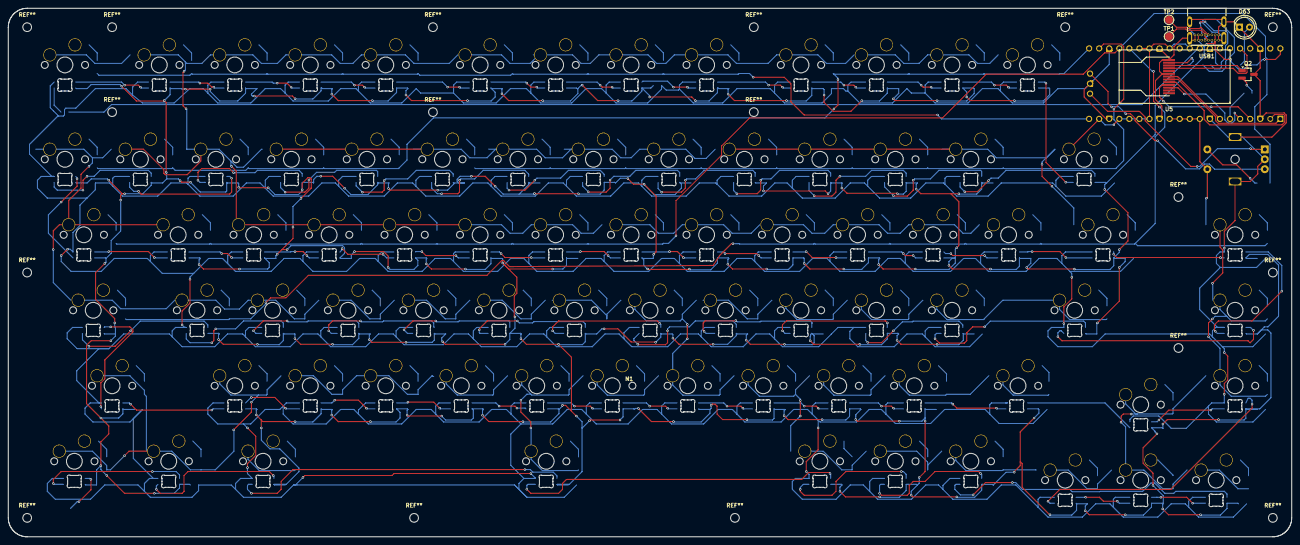
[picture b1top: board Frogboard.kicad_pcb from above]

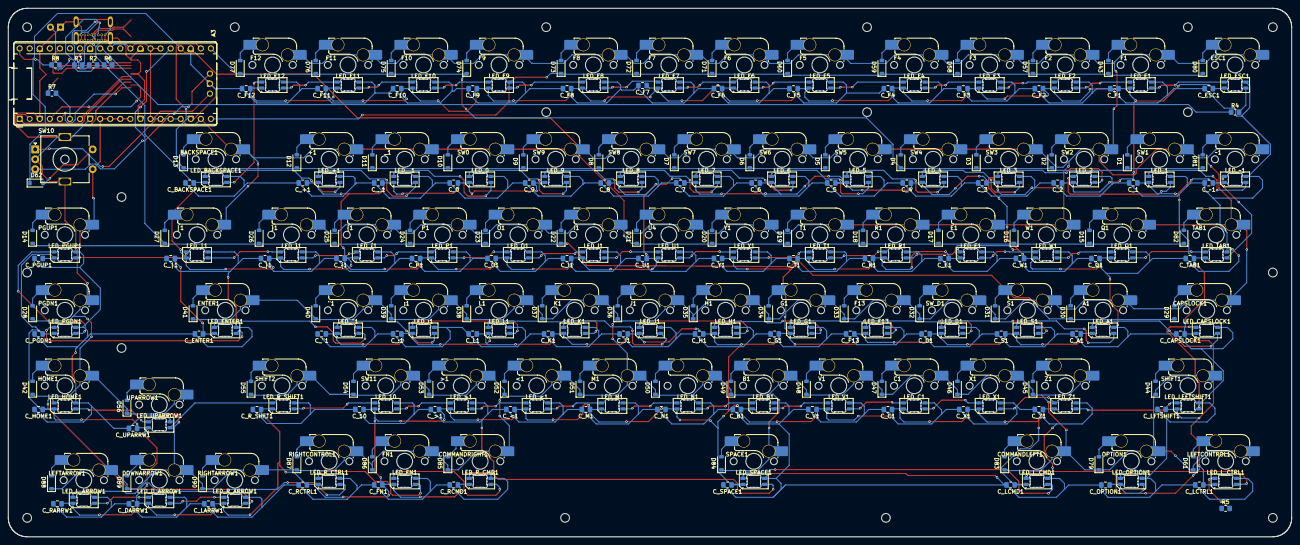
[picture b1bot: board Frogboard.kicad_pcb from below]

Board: 2 copper layers, 323.9 x 133.4 mm, 335 parts (329 on the bottom side), 187 nets.

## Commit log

2026-06-20 Upload CAD files
2026-06-20 Reupload pcb
2026-06-21 Added source files
2026-06-21 Create README.md with project overview
    Add initial README content explaining Keroppi features and purpose.
2026-06-21 Replace old image with new screenshot
    Updated images in the README for better clarity.
2026-06-21 Update BOM
2026-06-21 Revise BOM table format and add items
    Updated the Bill of Materials (BOM) table format for better readability and added missing items.
2026-06-21 Fix switch plate files
2026-06-22 Fixing the PCB files
2026-06-22 Fixing firmware files
2026-06-22 Fixed the CAD files
2026-06-22 Organized Files
2026-06-22 Revise assembly instructions and add images
    Updated assembly instructions for clarity and added images.
2026-06-22 Update README with new image and project rationale
    Added an image and a section explaining the purpose of Keroppi.
2026-06-22 Update instructions for attaching the top plate
    Removed mention of using glue and magnets for the top plate attachment.
2026-06-22 added top p late to the cad
2026-06-23 Added more spi stuff to the code
2026-06-23 Update PCB
2026-06-26 Update total cost and add jumper wires to README
2026-06-26 remove backups
